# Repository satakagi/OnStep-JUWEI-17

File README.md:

# OnStep-JUWEI-17

## Table of Contents

- [Introduction](#introduction)  
- [Why This Project?](#why-this-project)  
- [Disclaimer](#disclaimer)  
- [Features](#features)  
- [Hardware](#hardware)  
- [Firmware and Config.h Configuration](#firmware-and-configh-configuration)  
- [Usage](#usage)
- [Optional Feature: GPS Integration](#optional-feature-gps-integration)
- [Licensing](#licensing)  
- [Contribution & Support](#contribution--support)  
- [Contact](#contact)

---

## Introduction

This repository contains the open-source hardware (OSH) design files (KiCad project) for a custom **OnStep-JUWEI-17** controller board specifically tailored for the JUWEI-17 harmonic drive equatorial mount. This board provides a robust and configurable solution for upgrading the JUWEI-17 mount with the powerful OnStep firmware, enhancing its tracking accuracy and GoTo capabilities.

The circuit design is based on Roman Hujer's OnStep ESP32 Mini project, with specific adaptations for the JUWEI-17 mount — most notably, a hardware-controlled brake system.

---

## Why This Project?

This project addresses a critical issue for users in Japan (and possibly elsewhere):  
The stock JUWEI-17 controller often includes a Wi-Fi/Bluetooth module that lacks Japan's Radio Law certification ([技適マーク - Giteki Mark](https://www.tele.soumu.go.jp/e/adm/monitoring/illegal/monitoring_qa/index.htm)). Operating such a device is illegal in Japan.

This **OnStep-JUWEI-17** project offers a compliant alternative, using certified ESP32 and ESP8266 (ESP-12F) modules that include Giteki certification.  
The goal is to provide a legal, open, and high-performance upgrade path for the JUWEI-17 mount.

---

## Disclaimer

This project involves electronic assembly, including SMD components. Risks include, but are not limited to, electric shock, fire, damage, or injury.

**This project is provided "as is", with no warranty.**  
Use at your own risk. While the board relies mostly on through-hole parts, experience with hand-soldering wide-pitch SMD components is strongly recommended.

---

## Features

- Based on Roman Hujer's [OnStep ESP32 Mini](https://oshwlab.com/hujer.roman/onstep-esp-mini), functionally similar to OnStep MAX ESP3  
- Drop-in installation into the JUWEI-17 mount — no enclosure modifications required  
- Hardware-Controlled Brake System: Uses the ENABLE signal from motor drivers — no firmware tweaks needed  
- Open-Source Hardware: KiCad design files included

---

## Hardware

Custom PCB tailored for the JUWEI-17, based on the OnStep ESP32 Mini reference.  
Operates on 12V DC, supporting the original brake solenoid and motor drivers.

Refer to the [ASSEMBLY_GUIDE.md](ASSEMBLY_GUIDE.md) for detailed component list and assembly instructions.

### Manufacturing Files
The complete set of Gerber and drill files required for PCB manufacturing can be found in the [KiCad/gerber/](KiCad/gerber/) directory. These files are ready for submission to a PCB fabrication service.

Location: [KiCad/gerber/](KiCad/gerber/)

---

## **Images**

Here are some visual references for the project.

### **Assembled Board**

### **Installed on JUWEI-17 Mount**

### **PCB Design (Gerber View)**

### **Schematic**

### **PCB image**

---

## Firmware and Config.h Configuration

Uses standard OnStep firmware.  
Circuitry is nearly identical to the OnStep ESP32 Mini (minus the brake circuit), so you should reference that project for pin definitions and configurations.

---

### Specific Pin Map Settings

The pin map settings for this board are a modification of the standard Pins.MaxESP3.h file. They mirror the specific assignments documented by the [OnStep ESP32 Mini](https://oshwlab.com/hujer.roman/onstep-esp-mini) project on OSHWLab.

For your reference, the following assignments are replicated on this board:

- Aux7 = 36  
- OneWirePin = 15  
- ReticlePin = 19  
- TonePin = 2  
- PecPin = 39  
- AnalogPecPin = A3  

---

### ⚠️ Note for OnStepX Users

Variable names may differ in newer firmware.  
You will need to adapt these pin definitions to the appropriate structure in your version of Config.h and the corresponding Pins.*.h files.

---

### Gear Ratio Configuration

In Config.h, the gear ratio and motor settings must be exact. Errors will affect tracking and GoTo precision.

#### ⚠️ Important for JUWEI-17: "400:1" May Be Inaccurate

The JUWEI-17 mount is typically advertised with a gear system consisting of a 1:100 harmonic drive and a 1:4 pulley, for a total reduction of 400:1. The motors are standard NEMA17, with a 1.8°/step resolution.

However, based on user-reported data, the actual gear ratio appears to be 404:1, not 400:1.

From [Cloudy Nights post](https://www.cloudynights.com/topic/918425-juwei-17-mounts-on-aliexpress/?p=13665973):

- JUWEI original firmware uses 3591.111 steps/degree  
- Formula: (200 steps/rev × 16 microsteps × **101** x 4) ÷ 360 = 3591.111...

Harmonic drives can have ±1 variation depending on which spline is fixed.  
**Measure your actual gear ratio to ensure accuracy — do not trust online listings.**

---
<!-- TBD
### Sample Config Files

Sample Config.h and Pins.MaxESP3.h files are included in:

`Firmware_Examples/OnStepX_JUWEI-17/`

You must still modify them based on your stepper motors, gearing, and microstepping.

---
-->

### Important Notes on Configuration

- Ensure all pin/motor settings in Config.h and Pins.*.h match your board  
- Always re-upload firmware after making changes

---

## Tested and Confirmed Motor Driver Modules
The following motor driver modules have been successfully tested and confirmed to work with this board. The values in quotes ("...") are the corresponding AXIS?_DRIVER_MODEL settings in Config.h.

- BigTreeTech TMC2130 V3.0: "TMC2130"
- DRV8825 (Brand Unknown): "DRV8825"
- TMC2209 Module included with JUWEI-17 (Legacy Tested): "TMC2209S"

Note: All drivers were tested with 16 microsteps, which is the same setting as the original mount.

---

## Usage

To build and install this controller, follow the detailed instructions in [ASSEMBLY_GUIDE.md](ASSEMBLY_GUIDE.md).

---

## Optional Feature: GPS Integration
[A user successfully implemented](https://www.facebook.com/groups/349395118118532/posts/675489348842439/?comment_id=720520087672698) full GPS functionality by creatively repurposing existing pins on the AUX header and defining a Software Serial interface in OnStepX.

### Hardware and Wiring
- This method utilizes pins otherwise designated for PEC and the Reticle light:
- PPS Signal (Time Sync): Connect the GPS PPS (Pulse Per Second) output to the PEC Input (IO39).
- RX Data (Serial Data): Connect the GPS TX output (data) to the Reticle Pin (IO19).
- Critical Note: To ensure a clean signal path for the GPS, you must omit R20 and remove C7 during board assembly.

### Firmware Configuration
The GPS functionality must be enabled by defining the appropriate Software Serial pins within the OnStepX configuration file (Config.h).

---

## Licensing

This design is derived from the [OnStep ESP32 Mini](https://oshwlab.com/hujer.roman/onstep-esp-mini) project and is licensed under GPLv3.

✳️ _Note:_ Although GPLv3 is suitable for firmware, open hardware often benefits from dedicated licenses like the TAPR Open Hardware License (OHL). These better address physical product concerns such as patents and manufacturing rights.

---

## Contribution & Support

Contributions welcome!  
You can:

- Report bugs via GitHub Issues  
- Submit Pull Requests  
- Join discussion on Cloudy Nights forum

---

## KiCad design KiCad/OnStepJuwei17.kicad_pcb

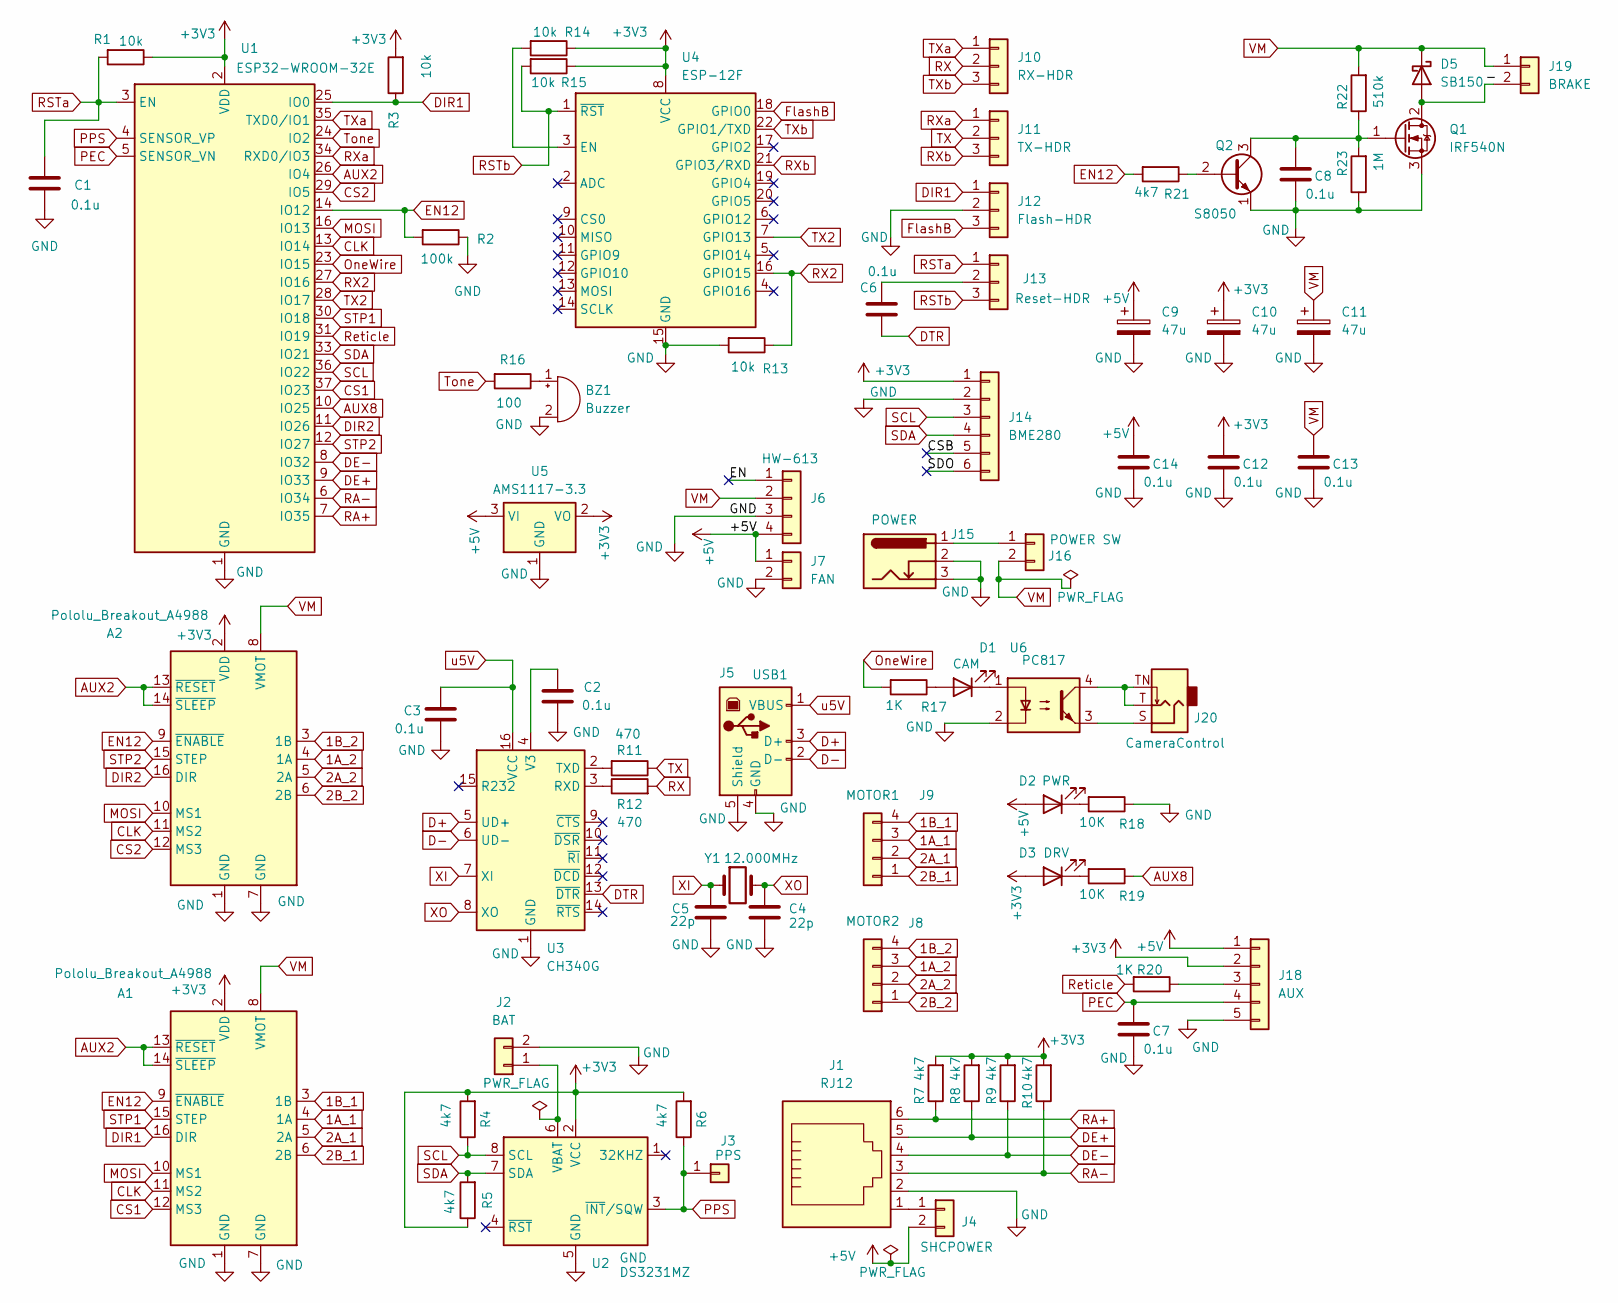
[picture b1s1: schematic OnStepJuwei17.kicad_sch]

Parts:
A1, A2: Pololu_Breakout_A4988; Pololu_Breakout-16_15.2x20.3mm
BZ1: Buzzer; Buzzer_12x9.5RM7.6
C1, C2, C3, C6, C7, C8, C12, C13, C14: 0.1u; C_Disc_D4.3mm_W1.9mm_P5.00mm
C4, C5: 22p; C_Disc_D4.3mm_W1.9mm_P5.00mm
C9, C10, C11: 47u; CP_Radial_D8.0mm_P5.00mm
D1: CAM; LED_D3.0mm
D2: PWR; LED_D3.0mm
D3: DRV; LED_D3.0mm
D5: SB150; D_DO-41_SOD81_P10.16mm_Horizontal
J1: RJ12; RJ25_Wayconn_MJEA-660X1_Horizontal
J2: BAT; PinHeader_1x02_P2.54mm_Vertical
J3: PPS; PinHeader_1x01_P2.54mm_Vertical
J4: SHCPOWER; PinHeader_1x02_P2.54mm_Vertical
J5: USB1; USB_B_Lumberg_2411_02_Horizontal
J6: HW-613
J7: FAN; PinHeader_1x02_P2.54mm_Vertical
J8: MOTOR2; PinHeader_1x04_P2.54mm_Vertical
J9: MOTOR1; PinHeader_1x04_P2.54mm_Vertical
J10: RX-HDR; PinHeader_1x03_P2.54mm_Vertical
J11: TX-HDR; PinHeader_1x03_P2.54mm_Vertical
J12: Flash-HDR; PinHeader_1x03_P2.54mm_Vertical
J13: Reset-HDR; PinHeader_1x03_P2.54mm_Vertical
J14: BME280; PinHeader_1x06_P2.54mm_Vertical
J15: POWER; BarrelJack_GCT_DCJ200-10-A_Horizontal
J16: POWER SW; PinHeader_1x02_P2.54mm_Vertical
J18: AUX; PinHeader_1x05_P2.54mm_Vertical
J19: BRAKE; PinHeader_1x02_P2.54mm_Vertical
J20: CameraControl; Jack_3.5mm_CUI_SJ1-3533NG_Horizontal_CircularHoles
Q1: IRF540N; TO-220-3_Vertical
Q2: S8050; TO-92_Inline
R1, R3, R13, R14, R15: 10k; R_Axial_DIN0204_L3.6mm_D1.6mm_P5.08mm_Horizontal
R2: 100k; R_Axial_DIN0204_L3.6mm_D1.6mm_P5.08mm_Horizontal
R4, R5, R6, R7, R8, R9, R10, R21: 4k7; R_Axial_DIN0204_L3.6mm_D1.6mm_P5.08mm_Horizontal
R11, R12: 470; R_Axial_DIN0204_L3.6mm_D1.6mm_P5.08mm_Horizontal
R16: 100; R_Axial_DIN0204_L3.6mm_D1.6mm_P5.08mm_Horizontal
R17, R20: 1K; R_Axial_DIN0204_L3.6mm_D1.6mm_P5.08mm_Horizontal
R18, R19: 10K; R_Axial_DIN0204_L3.6mm_D1.6mm_P5.08mm_Horizontal
R22: 510k; R_Axial_DIN0204_L3.6mm_D1.6mm_P5.08mm_Horizontal
R23: 1M; R_Axial_DIN0204_L3.6mm_D1.6mm_P5.08mm_Horizontal
U1: ESP32-WROOM-32E; ESP32-WROOM-32D
U2: DS3231MZ; SOIC-8_3.9x4.9mm_P1.27mm
U3: CH340G; SOIC-16_3.9x9.9mm_P1.27mm
U4: ESP-12F; ESP-12E
U5: AMS1117-3.3; SOT-223-3_TabPin2
U6: PC817; DIP-4_W7.62mm
Y1: 12.000MHz; Crystal_HC49-4H_Vertical

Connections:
1A_1: A1.4 (1A), J9.3
1A_2: A2.4 (1A), J8.3
1B_1: A1.3 (1B), J9.4
1B_2: A2.3 (1B), J8.4
2A_1: A1.5 (2A), J9.2
2A_2: A2.5 (2A), J8.2
2B_1: A1.6 (2B), J9.1
2B_2: A2.6 (2B), J8.1
+3V3: A1.2 (VDD), A2.2 (VDD), C10.1, C12.1, D3.2 (A), J14.1, J18.2, R1.1, R3.2, R4.2, R5.1, R6.2, R7.2, R8.2, R9.2, R10.2, R14.1, R15.1, U1.2 (VDD), U2.2 (VCC), U4.8 (VCC), U5.2 (VO)
+5V: C9.1, C14.1, D2.2 (A), J4.2, J6.4, J7.1, J18.1, U5.3 (VI)
/-: D5.2 (A), J19.2, Q1.2 (D)
/CSB: J14.5
/EN: J6.1
/SDO: J14.6
AUX2: A1.13 (~RESET), A1.14 (~SLEEP), A2.13 (~RESET), A2.14 (~SLEEP), U1.26 (IO4)
AUX8: R19.1, U1.10 (IO25)
CLK: A1.11 (MS2), A2.11 (MS2), U1.13 (IO14)
CS1: A1.12 (MS3), U1.37 (IO23)
CS2: A2.12 (MS3), U1.29 (IO5)
D+: J5.3 (D+), U3.5 (UD+)
D-: J5.2 (D-), U3.6 (UD-)
DE+: J1.5, R8.1, U1.9 (IO33)
DE-: J1.4, R9.1, U1.8 (IO32)
DIR1: A1.16 (DIR), J12.1, R3.1, U1.25 (IO0)
DIR2: A2.16 (DIR), U1.11 (IO26)
DTR: C6.1, U3.13 (~DTR)
EN12: A1.9 (~ENABLE), A2.9 (~ENABLE), R2.2, R21.2, U1.14 (IO12)
FlashB: J12.3, U4.18 (GPIO0)
GND: A1.1 (GND), A1.7 (GND), A2.1 (GND), A2.7 (GND), BZ1.2 (-), C1.2, C2.2, C3.2, C4.2, C5.2, C7.2, C8.2, C9.2, C10.2, C11.2, C12.2, C13.2, C14.2, J1.2, J2.2, J5.4 (GND), J5.5 (Shield), J6.3, J7.2, J12.2, J14.2, J15.2, J15.3, J18.5, Q1.3 (S), Q2.1 (E), R2.1, R13.2, R18.1, R23.1, U1.1 (GND), U1.15 (GND), U1.38 (GND), U1.39 (GND), U2.5 (GND), U3.1 (GND), U4.15 (GND), U5.1 (GND), U6.2
MOSI: A1.10 (MS1), A2.10 (MS1), U1.16 (IO13)
unnamed: BZ1.1 (+), R16.1
unnamed: D1.2 (A), R17.1
unnamed: D1.1 (K), U6.1
unnamed: D2.1 (K), R18.2
unnamed: D3.1 (K), R19.2
unnamed: J2.1, U2.6 (VBAT)
unnamed: J1.1, J4.1
unnamed: C6.2, J13.2
unnamed: J15.1, J16.1
unnamed: J18.3, R20.1
unnamed: J20.S, U6.3
unnamed: J20.T, J20.TN, U6.4
unnamed: C8.1, Q1.1 (G), Q2.3 (C), R22.1, R23.2
unnamed: Q2.2 (B), R21.1
unnamed: R12.1, U3.3 (RXD)
unnamed: R11.2, U3.2 (TXD)
unnamed: C2.1, U3.4 (V3)
unnamed: R14.2, U4.3 (EN)
OneWire: R17.2, U1.23 (IO15)
PEC: C7.1, J18.4, U1.5 (SENSOR_VN)
PPS: J3.1, R6.1, U1.4 (SENSOR_VP), U2.3 (~INT/SQW)
RA+: J1.6, R7.1, U1.7 (IO35)
RA-: J1.3, R10.1, U1.6 (IO34)
RSTa: C1.1, J13.1, R1.2, U1.3 (EN)
RSTb: J13.3, R15.2, U4.1 (~RST)
RX: J10.2, R12.2
RX2: R13.1, U1.27 (IO16), U4.16 (GPIO15)
RXa: J11.1, U1.34 (RXD0/IO3)
RXb: J11.3, U4.21 (GPIO3/RXD)
Reticle: R20.2, U1.31 (IO19)
SCL: J14.3, R4.1, U1.36 (IO22), U2.8 (SCL)
SDA: J14.4, R5.2, U1.33 (IO21), U2.7 (SDA)
STP1: A1.15 (STEP), U1.30 (IO18)
STP2: A2.15 (STEP), U1.12 (IO27)
TX: J11.2, R11.1
TX2: U1.28 (IO17), U4.7 (GPIO13)
TXa: J10.1, U1.35 (TXD0/IO1)
TXb: J10.3, U4.22 (GPIO1/TXD)
Tone: R16.2, U1.24 (IO2)
VM: A1.8 (VMOT), A2.8 (VMOT), C11.1, C13.1, D5.1 (K), J6.2, J16.2, J19.1, R22.2
XI: C5.1, U3.7 (XI), Y1.1
XO: C4.1, U3.8 (XO), Y1.2
u5V: C3.1, J5.1 (VBUS), U3.16 (VCC)

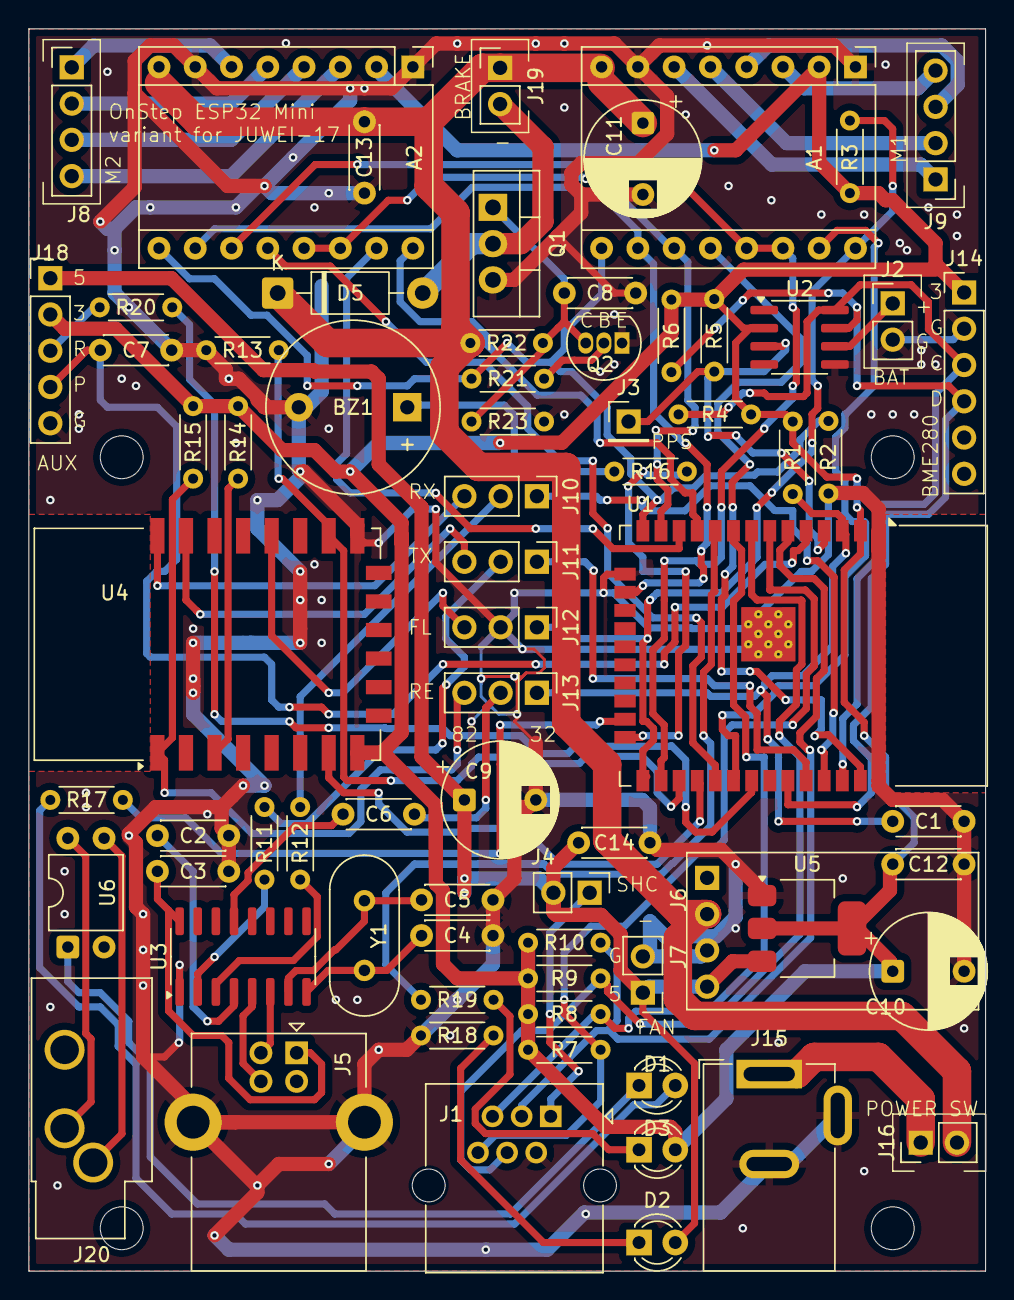
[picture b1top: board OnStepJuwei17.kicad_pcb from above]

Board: 2 copper layers, 67.0 x 87.0 mm, 72 parts (0 on the bottom side), 70 nets.

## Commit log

2025-08-01 Initial commit of OnStep-JUWEI-17 project files
